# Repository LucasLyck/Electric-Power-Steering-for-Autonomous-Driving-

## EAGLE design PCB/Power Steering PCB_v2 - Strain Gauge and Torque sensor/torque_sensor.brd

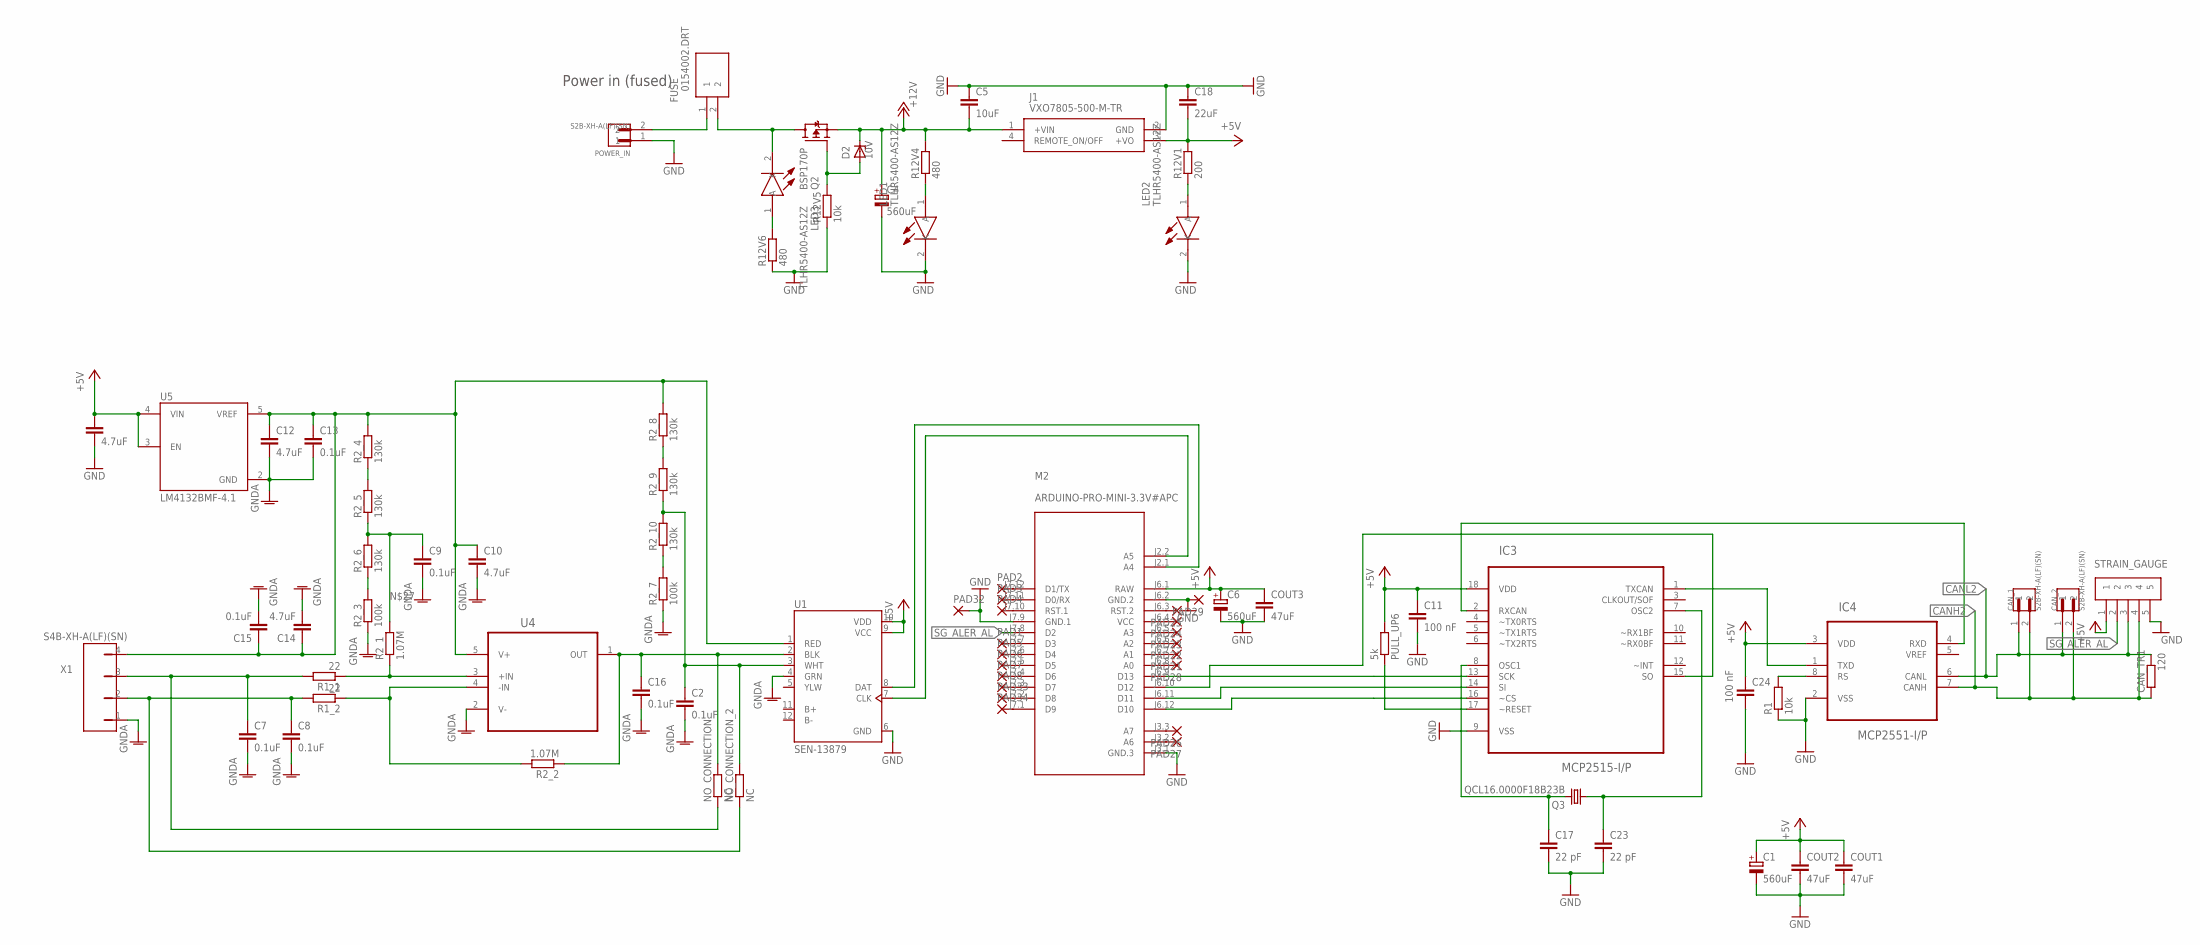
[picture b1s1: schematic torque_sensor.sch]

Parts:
C1, C4, C6: 560uF; PANASONIC_F
C2, C7, C8, C9, C13, C15, C16: 0.1uF; C0805
C3, C10, C12, C14: 4.7uF; C0805
C5: 10uF; C0805
C11, C24: 100 nF; C0805
C17, C23: 22 pF; C0805
C18: 22uF; C0805
CAN_1, CAN_2: S2B-XH-A(LF)(SN); JST_S2B-XH-A(LF)(SN)
CAN_TR1: 120; R0805
COUT1, COUT2, COUT3: 47uF; C0805
D2: 10V; SMB
FUSE: 0154002.DRT; FUSM9750X381N
IC3: MCP2515-I/P; DIP254P762X432-18
IC4: MCP2551-I/P; DIP254P762X432-8
J1: VXO7805-500-M-TR; VXO7805500MTR
LED1, LED2, LED3: TLHR5400-AS12Z; TLHR5400AS12Z
M2: ARDUINO-PRO-MINI-3.3V#APC; ARDUINO-PRO-MINI#APC
NO_CONNECTION: NC; R0805
NO_CONNECTION_2: NC; R0805
PAD1, PAD2, PAD3, PAD4, PAD5, PAD6, PAD7, PAD8, PAD21, PAD22, PAD23, PAD24, PAD25, PAD26, PAD27, PAD28, PAD29, PAD32, PAD33, PAD34: SMD2; SMD1,27-2,54
POWER_IN: S2B-XH-A(LF)(SN); JST_S2B-XH-A(LF)(SN)
PULL_UP6: 5k; R0805
Q2: BSP170P; SOT223
Q3: QCL16.0000F18B23B; HC49/S
R1, R12V5: 10k; R0805
R1_1, R1_2: 22; R0805
R2_1, R2_2: 1.07M; R0805
R2_3, R2_7: 100k; R0805
R2_4, R2_5, R2_6, R2_8, R2_9, R2_10: 130k; R0805
R12V1: 200; R0805
R12V4, R12V6: 480; R0805
STRAIN_GAUGE: S5B-XH-A(LF)(SN); JST_S5B-XH-A(LF)(SN)
U1: SEN-13879; SPARKFUN_SEN-13879
U4: LMP7731MF; SOT95P284X119-5N
U5: LM4132BMF-4.1; SOT95P280X145-5N
X1: S4B-XH-A(LF)(SN)

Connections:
+5V: C1.+, C3.1, C6.+, C11.1, C18.2, C24.1, COUT1.1, COUT2.1, COUT3.1, IC3.18 (VDD), IC4.3 (VDD), J1.3 (+VO), M2.J6.1 (RAW), PULL_UP6.2, R12V1.2, STRAIN_GAUGE.1, U1.9 (VCC), U1.10 (VDD), U5.3 (EN), U5.4 (VIN)
+12V: C4.+, C5.2, D2.C, J1.1 (+VIN), Q2.3 (S), R12V4.2
CANH2: CAN_1.2, CAN_2.2, CAN_TR1.1, IC4.7 (CANH), STRAIN_GAUGE.4
CANL2: CAN_1.1, CAN_2.1, CAN_TR1.2, IC4.6 (CANL), STRAIN_GAUGE.3
GND: C1.-, C3.2, C4.-, C5.1, C6.-, C11.2, C17.2, C18.1, C23.2, C24.2, COUT1.2, COUT2.2, COUT3.2, IC3.9 (VSS), IC4.2 (VSS), J1.2 (GND), LED1.2 (K), LED2.2 (K), M2.J3.1 (GND.3), M2.J6.2 (GND.2), M2.J7.9 (GND.1), PAD29.1, PAD32.1, POWER_IN.1, R1.1, R12V5.1, R12V6.1, STRAIN_GAUGE.5, U1.6 (GND)
GNDA: C2.2, C7.2, C8.2, C9.2, C10.2, C12.2, C13.2, C14.2, C15.2, C16.2, R2_3.1, R2_7.1, U1.4 (GRN), U4.2 (V-), U5.2 (GND), X1.1
unnamed: R2_8.1, R2_9.2
unnamed: LED2.1 (A), R12V1.1
unnamed: LED1.1 (A), R12V4.1
unnamed: C16.1, NO_CONNECTION.2, R2_2.1, U1.2 (BLK), U4.1 (OUT)
unnamed: R1_2.1, R2_2.2, U4.4 (-IN)
unnamed: M2.J7.12 (D1/TX), PAD2.1
unnamed: D2.A, Q2.1 (G), R12V5.2
unnamed: R2_7.2, R2_10.1
unnamed: C10.1, C12.1, C13.1, C14.1, C15.1, R2_4.2, R2_8.2, U1.1 (RED), U4.5 (V+), U5.5 (VREF), X1.4
unnamed: M2.J7.7 (D3), PAD1.1
unnamed: M2.J7.6 (D4), PAD5.1
unnamed: M2.J7.5 (D5), PAD6.1
unnamed: M2.J7.4 (D6), PAD7.1
unnamed: R1_1.1, R2_1.1, U4.3 (+IN)
unnamed: LED3.1 (A), R12V6.2
unnamed: M2.J2.2 (A5), U1.7 (CLK)
unnamed: M2.J7.3 (D7), PAD8.1
unnamed: M2.J7.11 (D0/RX), PAD3.1
unnamed: C2.1, NO_CONNECTION_2.2, R2_9.1, R2_10.2, U1.3 (WHT)
unnamed: M2.J2.1 (A4), U1.8 (DAT)
unnamed: FUSE.1, POWER_IN.2
unnamed: M2.J7.10 (RST.1), PAD4.1
unnamed: FUSE.2, LED3.2 (K), Q2.2 (D), Q2.4 (D)
unnamed: M2.J6.7 (A1), PAD21.1
unnamed: M2.J6.6 (A2), PAD22.1
unnamed: C9.1, R2_1.2, R2_5.1, R2_6.2
unnamed: M2.J6.5 (A3), PAD23.1
unnamed: M2.J6.4 (VCC), PAD24.1
unnamed: M2.J6.3 (RST.2), PAD25.1
unnamed: M2.J3.3 (A7), PAD26.1
unnamed: C8.1, NO_CONNECTION_2.1, R1_2.2, X1.2
unnamed: M2.J7.2 (D8), PAD33.1
unnamed: R2_4.1, R2_5.2
unnamed: IC3.15 (SO), M2.J6.10 (D12)
unnamed: IC3.13 (SCK), M2.J6.9 (D13)
unnamed: IC3.14 (SI), M2.J6.11 (D11)
unnamed: IC3.16 (~CS), M2.J6.12 (D10)
unnamed: M2.J3.2 (A6), PAD27.1
unnamed: M2.J6.8 (A0), PAD28.1
unnamed: R2_3.2, R2_6.1
unnamed: M2.J7.1 (D9), PAD34.1
unnamed: IC3.17 (~RESET), PULL_UP6.1
unnamed: C17.1, IC3.8 (OSC1), Q3.2
unnamed: C23.1, IC3.7 (OSC2), Q3.1
unnamed: IC4.8 (RS), R1.2
unnamed: IC3.2 (RXCAN), IC4.4 (RXD)
unnamed: IC3.1 (TXCAN), IC4.1 (TXD)
SG_ALER_AL: M2.J7.8 (D2), STRAIN_GAUGE.2
VCCINT4: C7.1, NO_CONNECTION.1, R1_1.2, X1.3

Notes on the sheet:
Power in (fused)

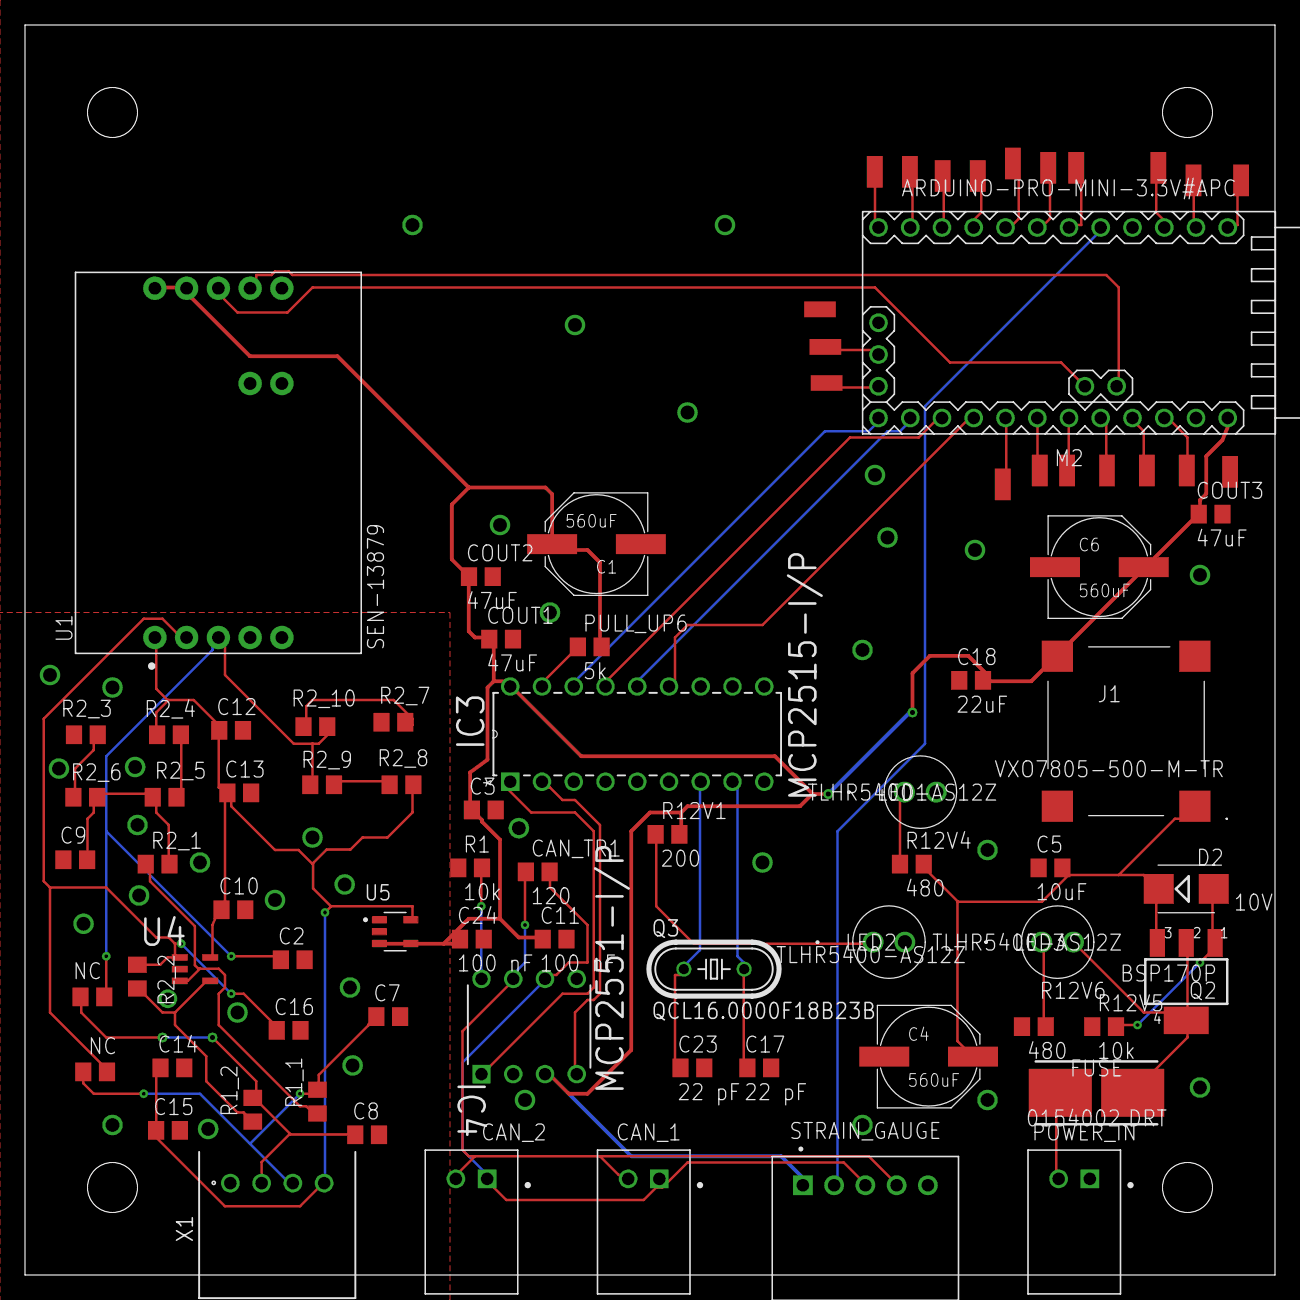
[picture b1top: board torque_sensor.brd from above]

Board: 2 copper layers, 100.0 x 100.0 mm, 83 parts (0 on the bottom side), 55 nets.

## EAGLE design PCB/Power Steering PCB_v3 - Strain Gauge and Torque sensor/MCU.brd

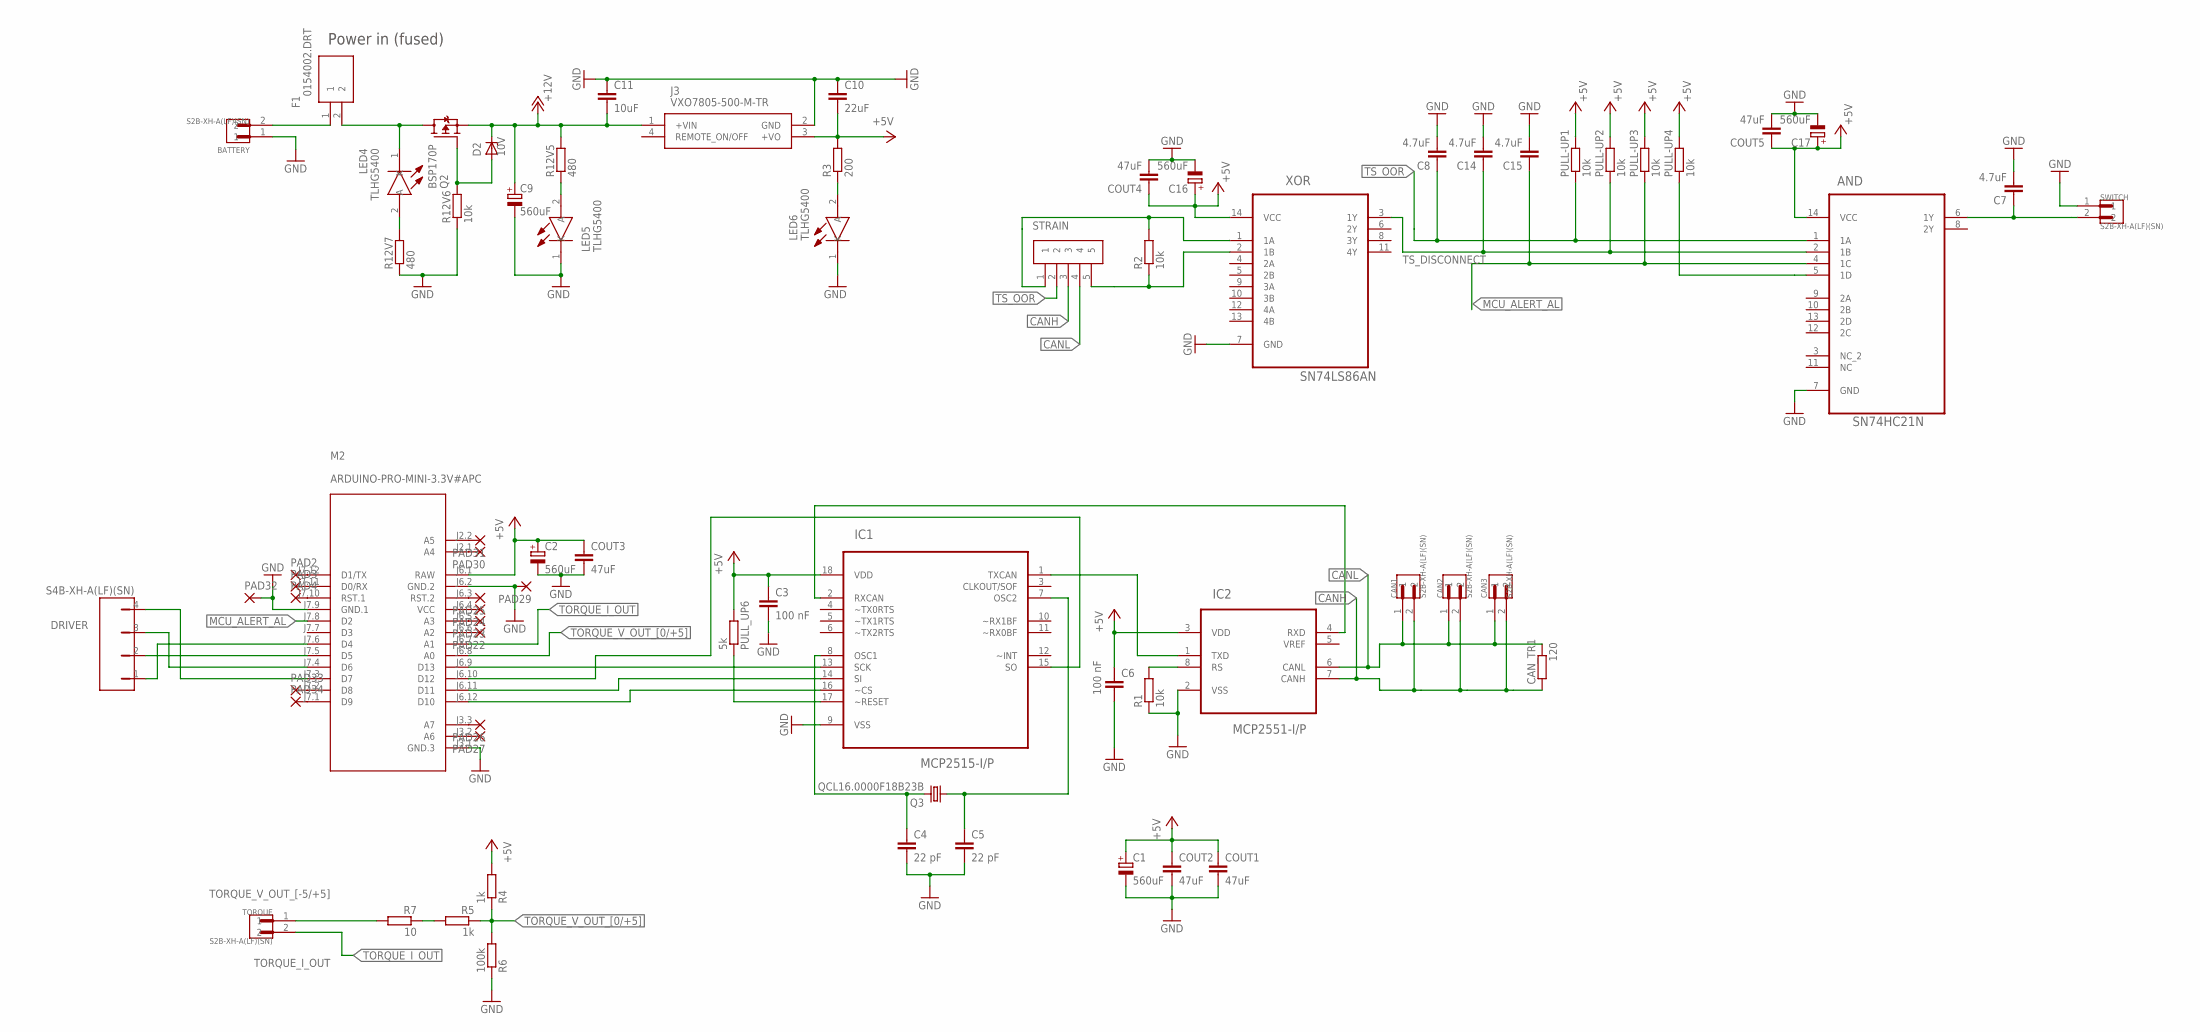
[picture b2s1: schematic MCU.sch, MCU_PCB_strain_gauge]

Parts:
AND: SN74HC21N; DIP254P762X508-14
BATTERY: S2B-XH-A(LF)(SN); JST_S2B-XH-A(LF)(SN)
C1, C2, C9, C16, C17: 560uF; PANASONIC_F
C3, C6: 100 nF; C0805
C4, C5: 22 pF; C0805
C7, C8, C14, C15: 4.7uF; C0805
C10: 22uF; C0805
C11: 10uF; C0805
CAN1, CAN2, CAN3: S2B-XH-A(LF)(SN); JST_S2B-XH-A(LF)(SN)
CAN_TR1: 120; R0805
COUT1, COUT2, COUT3, COUT4, COUT5: 47uF; C0805
D2: 10V; SMB
DRIVER: S4B-XH-A(LF)(SN)
F1: 0154002.DRT; FUSM9750X381N
IC1: MCP2515-I/P; DIP254P762X432-18
IC2: MCP2551-I/P; DIP254P762X432-8
J3: VXO7805-500-M-TR; VXO7805500MTR
LED4, LED5, LED6: TLHG5400
M2: ARDUINO-PRO-MINI-3.3V#APC; ARDUINO-PRO-MINI#APC
PAD2, PAD3, PAD4, PAD22, PAD23, PAD24, PAD25, PAD26, PAD27, PAD29, PAD30, PAD31, PAD32, PAD33, PAD34: SMD2; SMD1,27-2,54
PULL-UP1, PULL-UP2, PULL-UP3, PULL-UP4: 10k; R0805
PULL_UP6: 5k; R0805
Q2: BSP170P; SOT223
Q3: QCL16.0000F18B23B; HC49/S
R1, R2, R12V6: 10k; R0805
R3: 200; R0805
R4, R5: 1k; R0805
R6: 100k; R0805
R7: 10; R0805
R12V5, R12V7: 480; R0805
STRAIN: S5B-XH-A(LF)(SN); JST_S5B-XH-A(LF)(SN)
SWITCH: S2B-XH-A(LF)(SN); JST_S2B-XH-A(LF)(SN)
TORQUE: S2B-XH-A(LF)(SN); JST_S2B-XH-A(LF)(SN)
XOR: SN74LS86AN; DIP254P762X508-14

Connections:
+5V: AND.14 (VCC), C1.+, C2.+, C3.1, C6.1, C10.2, C16.+, C17.+, COUT1.1, COUT2.1, COUT3.1, COUT4.1, COUT5.1, IC1.18 (VDD), IC2.3 (VDD), J3.3 (+VO), M2.J6.1 (RAW), PULL-UP1.2, PULL-UP2.2, PULL-UP3.2, PULL-UP4.2, PULL_UP6.2, R3.2, R4.2, XOR.14 (VCC)
+12V: C9.+, C11.2, D2.C, J3.1 (+VIN), Q2.3 (S), R12V5.2
CANH: CAN1.2, CAN2.2, CAN3.2, CAN_TR1.1, IC2.7 (CANH), STRAIN.3
CANL: CAN1.1, CAN2.1, CAN3.1, CAN_TR1.2, IC2.6 (CANL), STRAIN.4
DRIVER_ALERT_AL: AND.5 (1D), PULL-UP4.1
GND: AND.7 (GND), BATTERY.1, C1.-, C2.-, C3.2, C4.2, C5.2, C6.2, C7.2, C8.2, C9.-, C10.1, C11.1, C14.2, C15.2, C16.-, C17.-, COUT1.2, COUT2.2, COUT3.2, COUT4.2, COUT5.2, IC1.9 (VSS), IC2.2 (VSS), J3.2 (GND), LED5.1 (K), LED6.1 (K), M2.J3.1 (GND.3), M2.J6.2 (GND.2), M2.J7.9 (GND.1), PAD29.1, PAD32.1, R1.1, R6.1, R12V6.1, R12V7.1, SWITCH.1, XOR.7 (GND)
MCU_ALERT_AL: AND.4 (1C), C15.1, M2.J7.8 (D2), PULL-UP3.1
unnamed: LED4.2 (A), R12V7.2
unnamed: DRIVER.4, M2.J7.3 (D7)
unnamed: M2.J7.12 (D1/TX), PAD2.1
unnamed: M2.J7.11 (D0/RX), PAD3.1
unnamed: D2.A, Q2.1 (G), R12V6.2
unnamed: BATTERY.2, F1.1
unnamed: F1.2, LED4.1 (K), Q2.2 (D), Q2.4 (D)
unnamed: M2.J7.10 (RST.1), PAD4.1
unnamed: DRIVER.1, M2.J7.6 (D4)
unnamed: M2.J6.6 (A2), PAD22.1
unnamed: M2.J6.5 (A3), PAD23.1
unnamed: M2.J6.4 (VCC), PAD24.1
unnamed: IC1.15 (SO), M2.J6.10 (D12)
unnamed: M2.J6.3 (RST.2), PAD25.1
unnamed: DRIVER.2, M2.J7.5 (D5)
unnamed: R5.2, R7.1
unnamed: M2.J3.3 (A7), PAD26.1
unnamed: LED5.2 (A), R12V5.1
unnamed: LED6.2 (A), R3.1
unnamed: IC1.13 (SCK), M2.J6.9 (D13)
unnamed: IC1.14 (SI), M2.J6.11 (D11)
unnamed: IC1.16 (~CS), M2.J6.12 (D10)
unnamed: DRIVER.3, M2.J7.4 (D6)
unnamed: M2.J3.2 (A6), PAD27.1
unnamed: M2.J2.1 (A4), PAD30.1
unnamed: M2.J2.2 (A5), PAD31.1
unnamed: M2.J7.2 (D8), PAD33.1
unnamed: M2.J7.1 (D9), PAD34.1
unnamed: IC1.17 (~RESET), PULL_UP6.1
unnamed: C4.1, IC1.8 (OSC1), Q3.2
unnamed: C5.1, IC1.7 (OSC2), Q3.1
unnamed: IC2.8 (RS), R1.2
unnamed: IC1.2 (RXCAN), IC2.4 (RXD)
unnamed: R2.2, STRAIN.1, XOR.1 (1A)
unnamed: AND.6 (1Y), C7.1, SWITCH.2
unnamed: R2.1, STRAIN.5, XOR.2 (1B)
unnamed: IC1.1 (TXCAN), IC2.1 (TXD)
TORQUE_I_OUT: M2.J6.7 (A1), TORQUE.2
TORQUE_V_OUT_[0/+5]: M2.J6.8 (A0), R4.1, R5.1, R6.2
TORQUE_V_OUT_[-5/+5]: R7.2, TORQUE.1
TS_DISCONNECT: AND.2 (1B), C14.1, PULL-UP2.1, XOR.3 (1Y)
TS_OOR: AND.1 (1A), C8.1, PULL-UP1.1, STRAIN.2

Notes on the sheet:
Power in (fused)

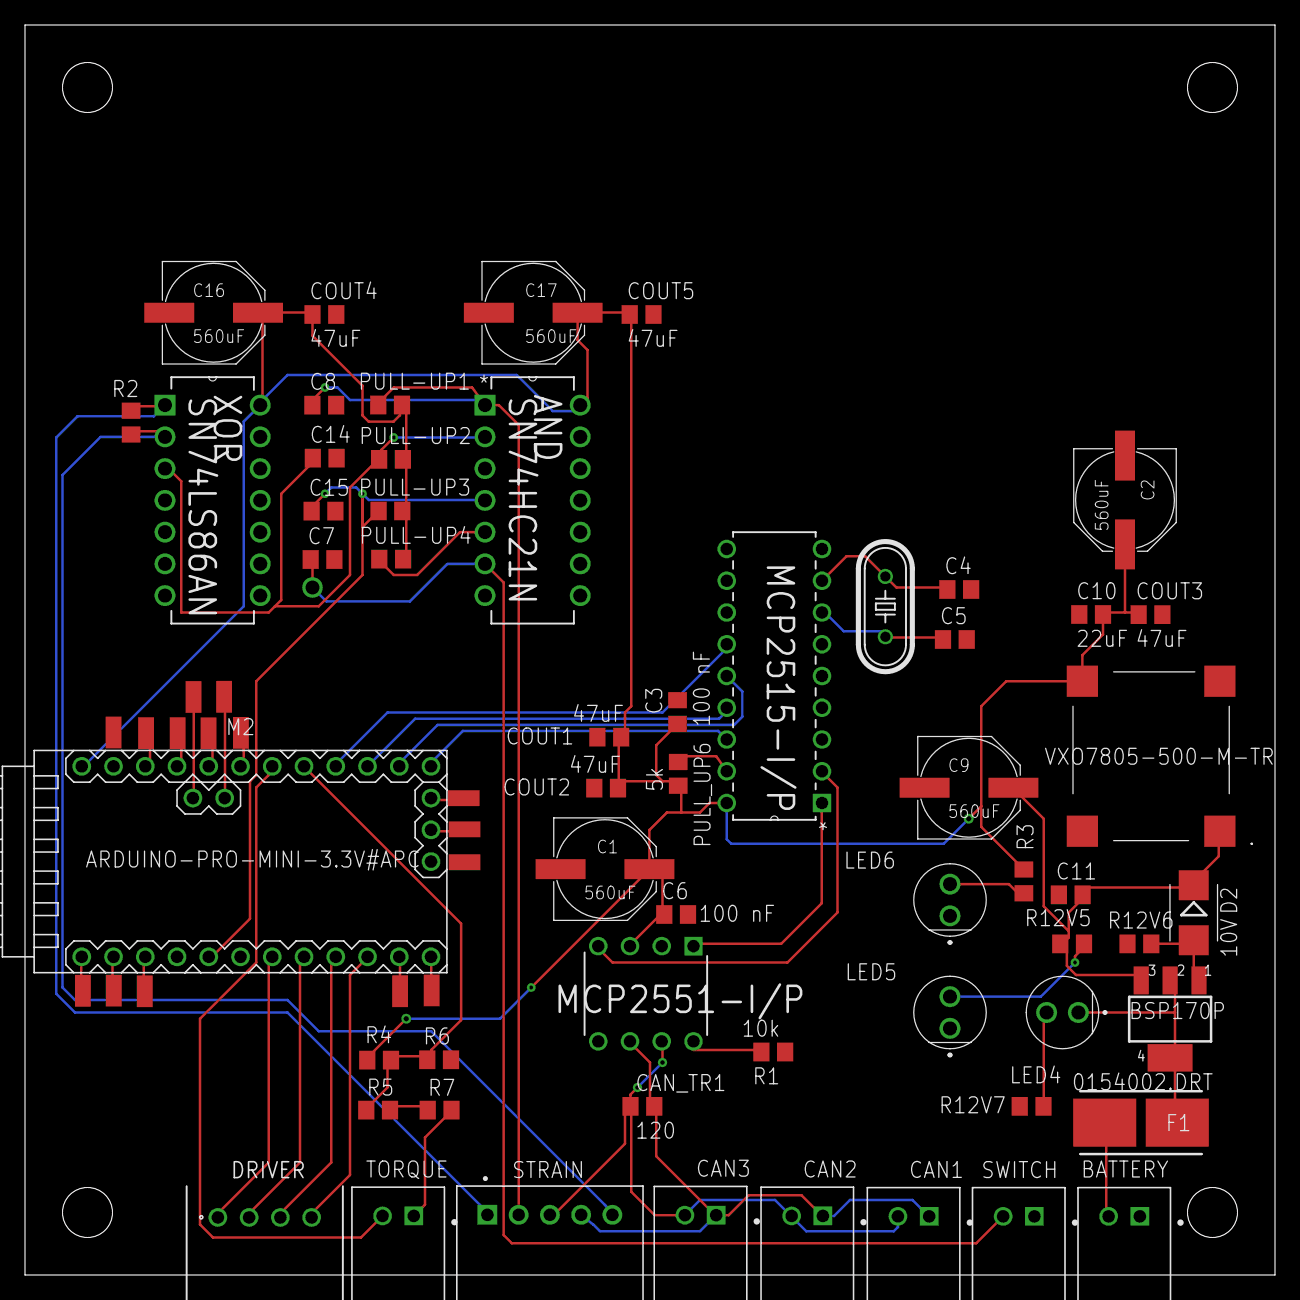
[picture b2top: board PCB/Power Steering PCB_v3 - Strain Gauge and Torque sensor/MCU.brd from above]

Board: 2 copper layers, 100.0 x 100.0 mm, 72 parts (0 on the bottom side), 49 nets.

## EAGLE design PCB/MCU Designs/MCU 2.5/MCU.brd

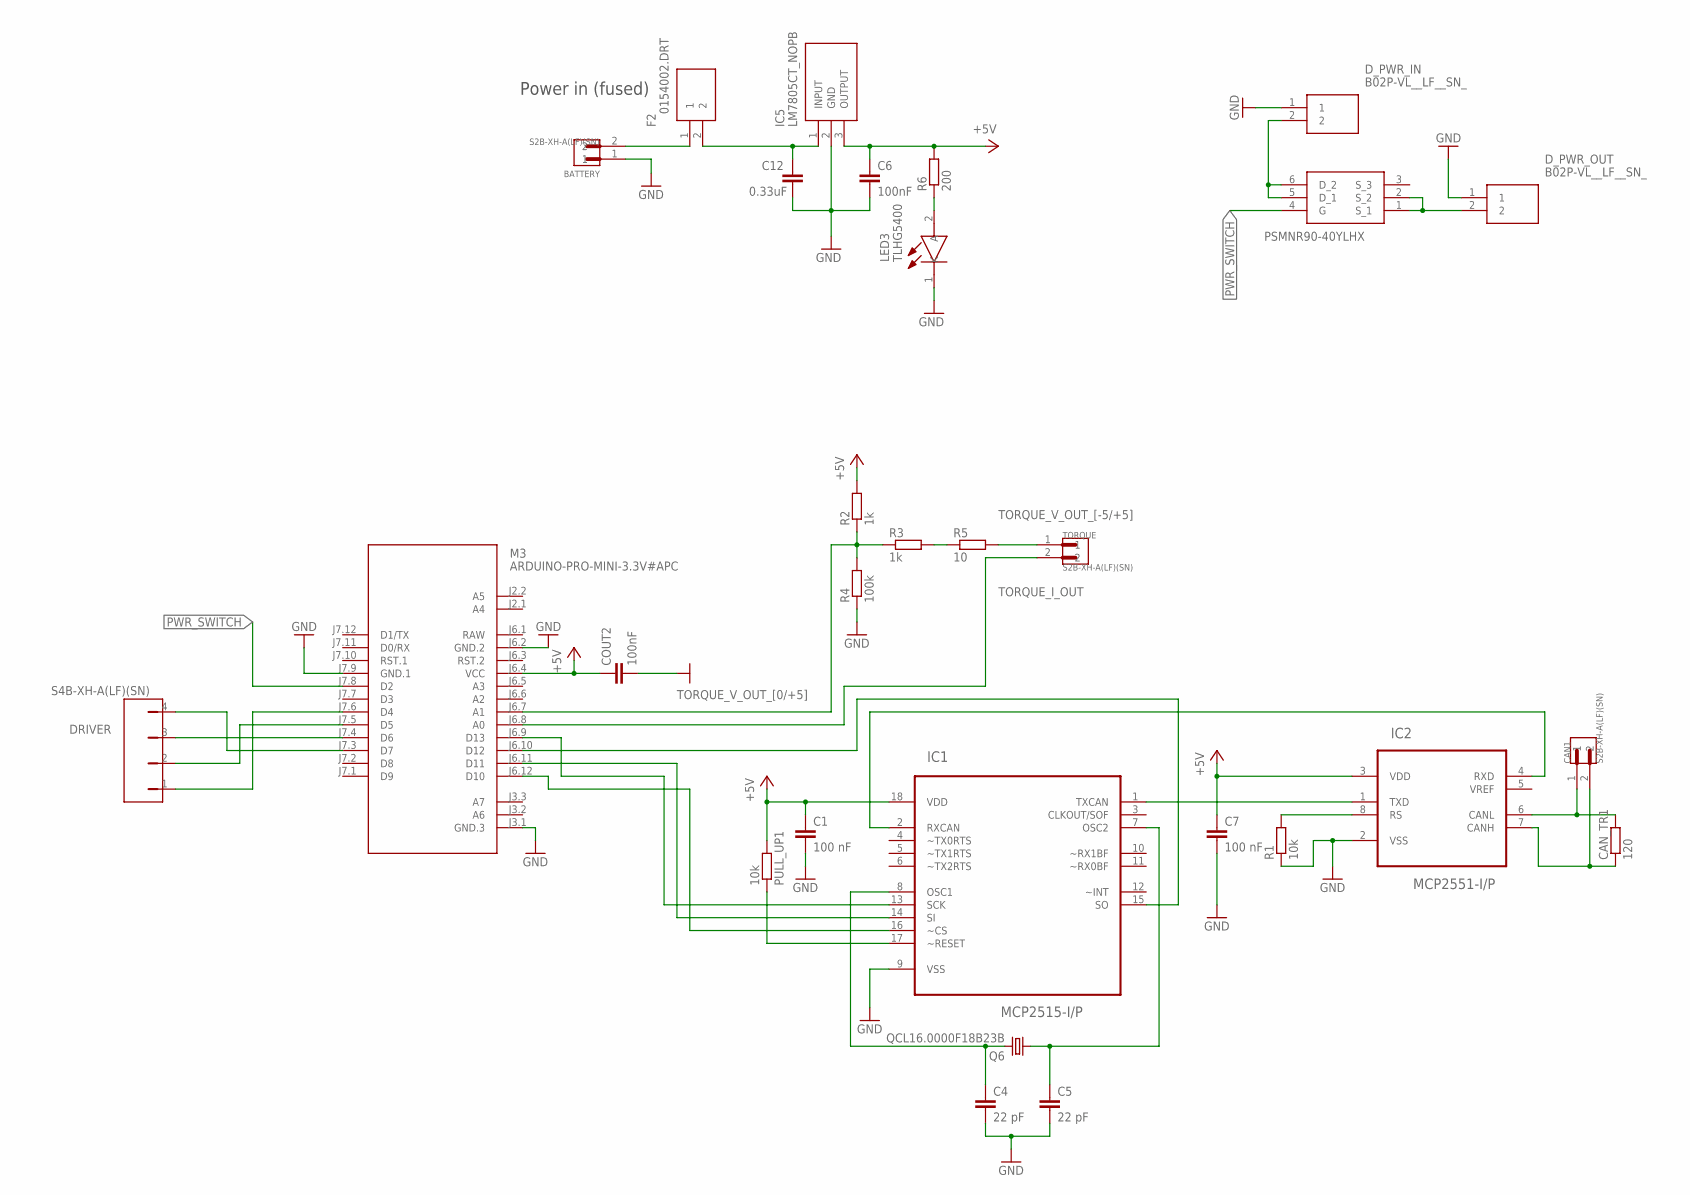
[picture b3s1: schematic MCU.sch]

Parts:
BATTERY: S2B-XH-A(LF)(SN); JST_S2B-XH-A(LF)(SN)
C1, C7: 100 nF; C0805
C4, C5: 22 pF; C0805
C6: 100nF; C0805
C12: 0.33uF; C0805
CAN1: S2B-XH-A(LF)(SN); JST_S2B-XH-A(LF)(SN)
CAN_TR1: 120; R0805
COUT2: 100nF; C0805
DRIVER: S4B-XH-A(LF)(SN)
D_PWR_IN: B02P-VL__LF__SN_; SHDR2W180P0X620_1X2_1340X1320X
D_PWR_OUT: B02P-VL__LF__SN_; SHDR2W180P0X620_1X2_1340X1320X
F2: 0154002.DRT; FUSM9750X381N
IC1: MCP2515-I/P; DIP254P762X432-18
IC2: MCP2551-I/P; DIP254P762X432-8
IC5: LM7805CT_NOPB; TO254P470X1028X1955-3P
LED3: TLHG5400
M3: ARDUINO-PRO-MINI-3.3V#APC; ARDUINO-PRO-MINI#APC
PULL_UP1: 10k; R0805
Q1: PSMNR90-40YLHX; PSMNR9040YLHX
Q6: QCL16.0000F18B23B; HC49/S
R1: 10k; R0805
R2, R3: 1k; R0805
R4: 100k; R0805
R5: 10; R0805
R6: 200; R0805
TORQUE: S2B-XH-A(LF)(SN); JST_S2B-XH-A(LF)(SN)

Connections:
+5V: C1.1, C6.1, C7.1, COUT2.1, IC1.18 (VDD), IC2.3 (VDD), IC5.3 (OUTPUT), M3.J6.4 (VCC), PULL_UP1.2, R2.2, R6.2
CANH1: CAN1.1, CAN_TR1.2, IC2.6 (CANL)
CANL1: CAN1.2, CAN_TR1.1, IC2.7 (CANH)
DRAIN: D_PWR_IN.2, Q1.5 (D_1), Q1.6 (D_2)
GND: BATTERY.1, C1.2, C4.2, C5.2, C6.2, C7.2, C12.2, COUT2.2, D_PWR_IN.1, D_PWR_OUT.1, IC1.9 (VSS), IC2.2 (VSS), IC5.2 (GND), LED3.1 (K), M3.J3.1 (GND.3), M3.J6.2 (GND.2), M3.J7.9 (GND.1), R1.1, R4.1
unnamed: DRIVER.4, M3.J7.3 (D7)
unnamed: DRIVER.2, M3.J7.5 (D5)
unnamed: C5.1, IC1.7 (OSC2), Q6.1
unnamed: DRIVER.3, M3.J7.4 (D6)
unnamed: IC1.17 (~RESET), PULL_UP1.1
unnamed: DRIVER.1, M3.J7.6 (D4)
unnamed: R3.2, R5.1
unnamed: BATTERY.2, F2.1
unnamed: LED3.2 (A), R6.1
unnamed: C12.1, F2.2, IC5.1 (INPUT)
unnamed: IC1.1 (TXCAN), IC2.1 (TXD)
unnamed: IC1.2 (RXCAN), IC2.4 (RXD)
unnamed: C4.1, IC1.8 (OSC1), Q6.2
unnamed: IC2.8 (RS), R1.2
unnamed: IC1.15 (SO), M3.J6.10 (D12)
unnamed: IC1.14 (SI), M3.J6.11 (D11)
unnamed: IC1.16 (~CS), M3.J6.12 (D10)
unnamed: IC1.13 (SCK), M3.J6.9 (D13)
PWR_SWITCH: M3.J7.8 (D2), Q1.4 (G)
RAW: M3.J6.1 (RAW)
SOURCE: D_PWR_OUT.2, Q1.1 (S_1), Q1.2 (S_2)
TORQUE_I_OUT: M3.J6.8 (A0), TORQUE.2
TORQUE_V_OUT_[0/+5]: M3.J6.7 (A1), R2.1, R3.1, R4.2
TORQUE_V_OUT_[-5/+5]: R5.2, TORQUE.1

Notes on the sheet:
Power in (fused)

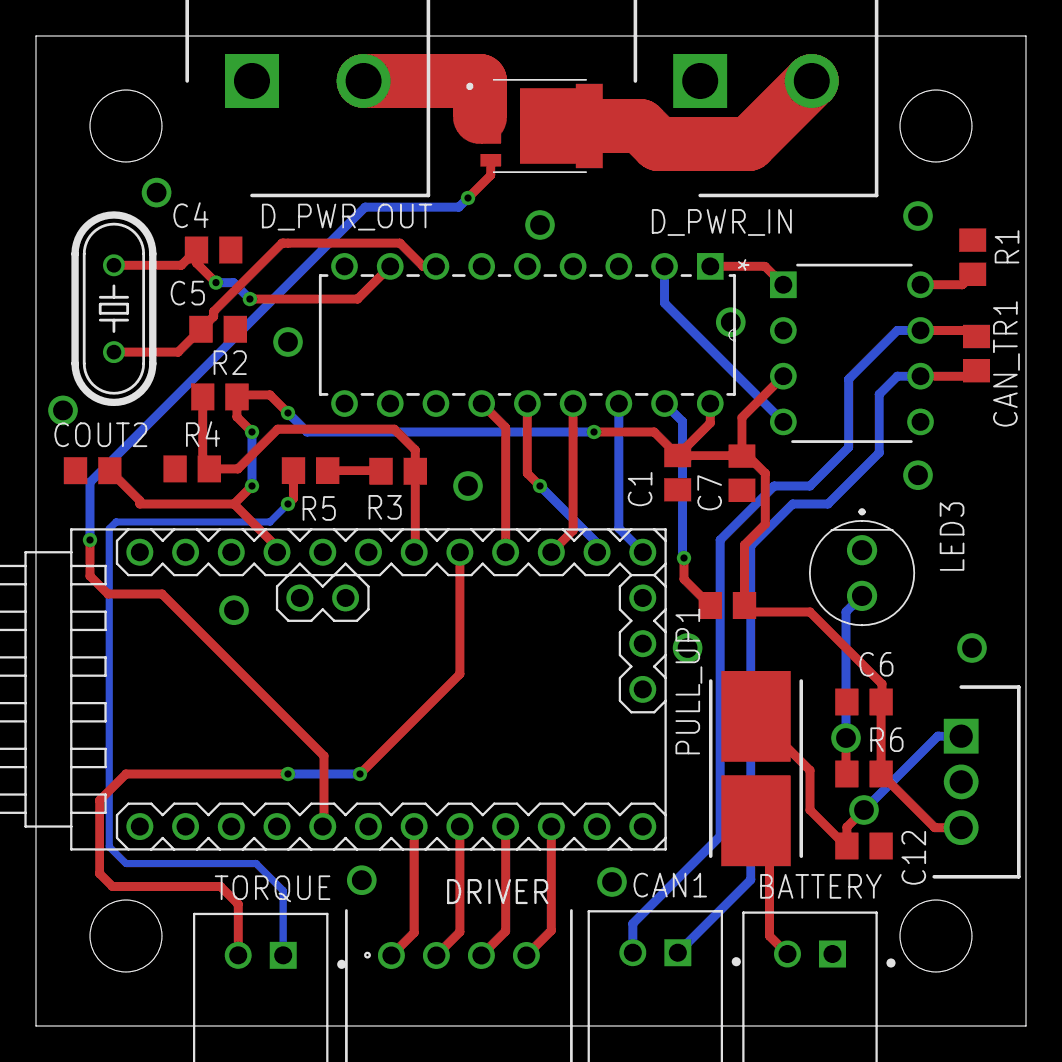
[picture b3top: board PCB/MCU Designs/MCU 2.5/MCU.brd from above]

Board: 2 copper layers, 55.0 x 55.0 mm, 29 parts (0 on the bottom side), 28 nets.

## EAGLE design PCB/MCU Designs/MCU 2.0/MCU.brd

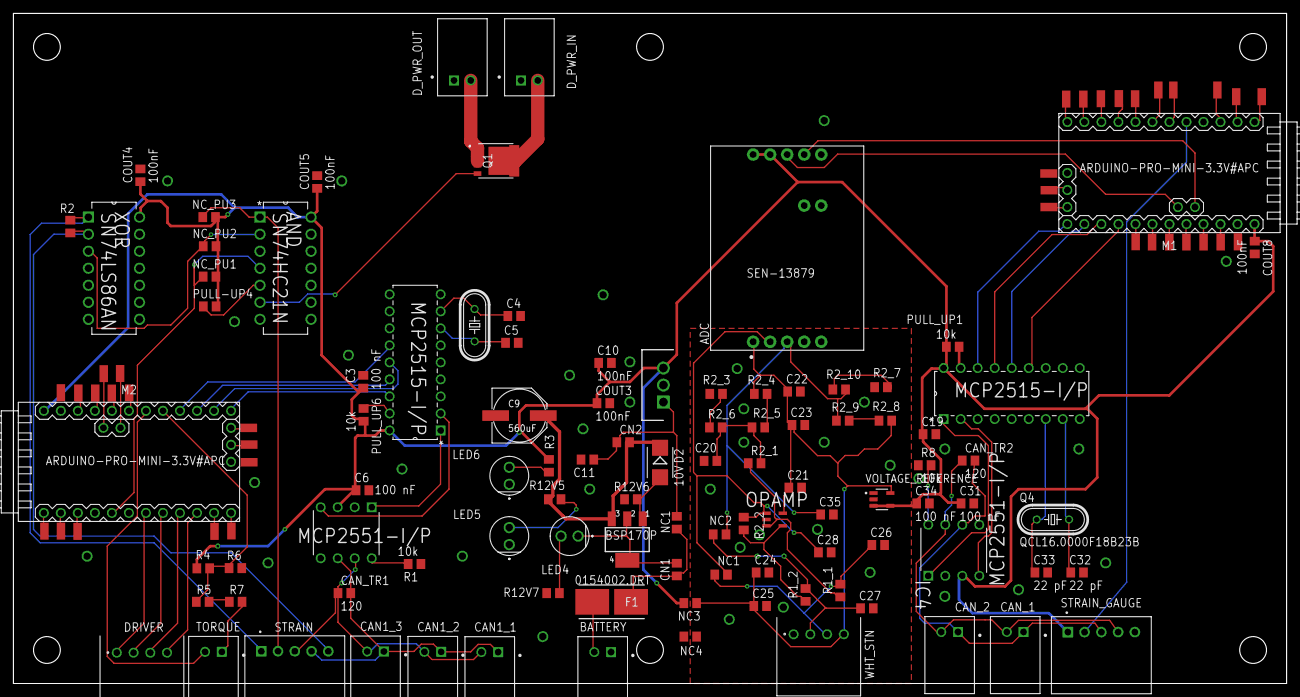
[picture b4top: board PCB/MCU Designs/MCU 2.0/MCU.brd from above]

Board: 2 copper layers, 190.0 x 100.0 mm, 133 parts (0 on the bottom side), 99 nets.

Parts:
ADC: SEN-13879; SPARKFUN_SEN-13879
AND: SN74HC21N; DIP254P762X508-14
BATTERY: S2B-XH-A(LF)(SN); JST_S2B-XH-A(LF)(SN)
C3, C6, C31, C34: 100 nF; C0805
C4, C5, C32, C33: 22 pF; C0805
C9: 560uF; PANASONIC_F
C10, C20, C23, C25, C26, C27, C28, C35: 100nF; C0805
C11: 0.33uF; C0805
C19, C21, C22, C24: 4.7uF; C0805
CAN1_1, CAN1_2, CAN1_3: S2B-XH-A(LF)(SN); JST_S2B-XH-A(LF)(SN)
CAN_1, CAN_2: S2B-XH-A(LF)(SN); JST_S2B-XH-A(LF)(SN)
CAN_TR1, CAN_TR2: 120; R0805
CN1, CN2: 10k; R0805
COUT3, COUT4, COUT5, COUT8: 100nF; C0805
D2: 10V; SMB
DRIVER: S4B-XH-A(LF)(SN)
D_PWR_IN: S2B-XH-A(LF)(SN); JST_S2B-XH-A(LF)(SN)
D_PWR_OUT: S2B-XH-A(LF)(SN); JST_S2B-XH-A(LF)(SN)
F1: 0154002.DRT; FUSM9750X381N
IC1, IC3: MCP2515-I/P; DIP254P762X432-18
IC2, IC4: MCP2551-I/P; DIP254P762X432-8
IC5: LM7805CT_NOPB; TO254P470X1028X1955-3P
LED4, LED5, LED6: TLHG5400
M1, M2: ARDUINO-PRO-MINI-3.3V#APC; ARDUINO-PRO-MINI#APC
NC1: 10k; R0805
NC3, NC4: R0805
NC_PU1, NC_PU2, NC_PU3: 10k; R0805
NO_CONNECTION: NC1; R0805
NO_CONNECTION_2: NC2; R0805
OPAMP: LMP7731MF; SOT95P284X119-5N
PAD1, PAD2, PAD3, PAD4, PAD5, PAD6, PAD7, PAD8, PAD9, PAD10, PAD11, PAD12, PAD13, PAD14, PAD15, PAD16, PAD17, PAD18, PAD19, PAD20, PAD21, PAD22, PAD23, PAD24, PAD25, PAD26, PAD27, PAD28, PAD29, PAD30, PAD31, PAD32, PAD33, PAD34, PAD35: SMD1,27-2,54
PULL-UP4: 10k; R0805
PULL_UP1, PULL_UP6: 10k; R0805
Q1: PSMNR90-40YLHX; PSMNR9040YLHX
Q2: BSP170P; SOT223
Q3, Q4: QCL16.0000F18B23B; HC49/S
R1, R2, R8, R12V6: 10k; R0805
R1_1, R1_2: 22; R0805
R2_1, R2_2: 1.07M; R0805
R2_3, R2_7, R6: 100k; R0805
R2_4, R2_5, R2_6, R2_8, R2_9, R2_10: 130k; R0805
R3: 200; R0805
R4, R5: 1k; R0805
R7: 10; R0805
R12V5, R12V7: 480; R0805
STRAIN: S5B-XH-A(LF)(SN); JST_S5B-XH-A(LF)(SN)
STRAIN_GAUGE: S5B-XH-A(LF)(SN); JST_S5B-XH-A(LF)(SN)
TORQUE: S2B-XH-A(LF)(SN); JST_S2B-XH-A(LF)(SN)
VOLTAGE_REFERENCE: LM4132BMF-4.1; SOT95P280X145-5N
WHT_STN: S4B-XH-A(LF)(SN)
XOR: SN74LS86AN; DIP254P762X508-14

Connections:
+5V: ADC.9, ADC.10, AND.14, C3.1, C6.1, C10.1, C19.1, C31.1, C34.1, COUT3.1, COUT4.1, COUT5.1, COUT8.1, IC1.18, IC2.3, IC3.18, IC4.3, IC5.3, M1.J6.1, M2.J6.1, NC3.2, NC_PU1.2, NC_PU2.2, NC_PU3.2, PULL-UP4.2, PULL_UP1.2, PULL_UP6.2, R3.2, R4.2, STRAIN_GAUGE.1, VOLTAGE_REFERENCE.3, VOLTAGE_REFERENCE.4, XOR.14
+12V: C9.+, CN2.2, D2.C, Q2.3, R12V5.2
CANH1: CAN1_1.2, CAN1_2.2, CAN1_3.2, CAN_TR1.1, IC2.7, STRAIN.3
CANH2: CAN_1.2, CAN_2.2, CAN_TR2.1, IC4.7, STRAIN_GAUGE.4
CANL1: CAN1_1.1, CAN1_2.1, CAN1_3.1, CAN_TR1.2, IC2.6, STRAIN.4
CANL2: CAN_1.1, CAN_2.1, CAN_TR2.2, IC4.6, STRAIN_GAUGE.3
DRAIN: D_PWR_IN.2, Q1.5, Q1.6
DRIVER_ALERT_AL: AND.5, PULL-UP4.1
GND: ADC.6, AND.7, BATTERY.1, C3.2, C4.2, C5.2, C6.2, C9.-, C10.2, C11.2, C19.2, C31.2, C32.2, C33.2, C34.2, COUT3.2, COUT4.2, COUT5.2, COUT8.2, D_PWR_IN.1, D_PWR_OUT.1, IC1.9, IC2.2, IC3.9, IC4.2, LED5.1, LED6.1, M1.J3.1, M1.J6.2, M1.J7.9, M2.J3.1, M2.J6.2, M2.J7.9, NC4.1, PAD13.1, PAD14.1, PAD29.1, PAD32.1, R1.1, R6.1, R8.1, R12V6.1, R12V7.1, STRAIN_GAUGE.5, XOR.7
GNDA: ADC.4, C20.2, C21.2, C22.2, C23.2, C24.2, C25.2, C26.2, C27.2, C28.2, C35.2, NC4.2, OPAMP.2, R2_3.1, R2_7.1, VOLTAGE_REFERENCE.2, WHT_STN.1
MCU_ALERT_AL: AND.4, M2.J7.8, NC_PU1.1
unnamed: LED4.2, R12V7.2
unnamed: DRIVER.4, M2.J7.3
unnamed: M2.J7.12, PAD2.1
unnamed: M2.J7.11, PAD3.1
unnamed: D2.A, Q2.1, R12V6.2
unnamed: BATTERY.2, F1.1
unnamed: CN1.1, LED4.1, Q2.2, Q2.4
unnamed: M2.J7.10, PAD4.1
unnamed: DRIVER.1, M2.J7.6
unnamed: M2.J6.6, PAD22.1
unnamed: M2.J6.5, PAD23.1
unnamed: M2.J6.4, PAD24.1
unnamed: IC1.15, M2.J6.10
unnamed: M2.J6.3, PAD25.1
unnamed: DRIVER.2, M2.J7.5
unnamed: R5.2, R7.1
unnamed: M2.J3.3, PAD26.1
unnamed: LED5.2, R12V5.1
unnamed: LED6.2, R3.1
unnamed: IC1.13, M2.J6.9
unnamed: IC1.14, M2.J6.11
unnamed: IC1.16, M2.J6.12
unnamed: DRIVER.3, M2.J7.4
unnamed: CN1.2, F1.2, NC1.2
unnamed: C11.1, CN2.1, IC5.1, NC1.1
unnamed: C20.1, R2_1.2, R2_5.1, R2_6.2
unnamed: ADC.2, C28.1, NO_CONNECTION.2, OPAMP.1, R2_2.1
unnamed: OPAMP.4, R1_2.1, R2_2.2
unnamed: OPAMP.3, R1_1.1, R2_1.1
unnamed: R2_3.2, R2_6.1
unnamed: M1.J7.12, PAD1.1
unnamed: M1.J7.11, PAD5.1
unnamed: M1.J7.10, PAD6.1
unnamed: R2_4.1, R2_5.2
unnamed: M1.J6.7, PAD21.1
unnamed: M1.J6.6, PAD7.1
unnamed: M1.J6.5, PAD8.1
unnamed: M1.J6.4, PAD9.1
unnamed: M2.J3.2, PAD27.1
unnamed: M1.J6.3, PAD10.1
unnamed: M2.J2.1, PAD30.1
unnamed: M1.J3.3, PAD11.1
unnamed: M1.J3.2, PAD12.1
unnamed: M1.J6.8, PAD28.1
unnamed: M1.J7.2, PAD15.1
unnamed: M1.J7.1, PAD16.1
unnamed: IC3.17, PULL_UP1.1
unnamed: M2.J2.2, PAD31.1
unnamed: C32.1, IC3.8, Q4.2
unnamed: C33.1, IC3.7, Q4.1
unnamed: IC4.8, R8.2
unnamed: IC3.2, IC4.4
unnamed: M2.J7.2, PAD33.1
unnamed: M2.J7.1, PAD34.1
unnamed: IC1.17, PULL_UP6.1
unnamed: IC3.1, IC4.1
unnamed: C4.1, IC1.8, Q3.2
unnamed: C5.1, IC1.7, Q3.1
unnamed: IC2.8, R1.2
unnamed: IC3.15, M1.J6.10
unnamed: IC1.2, IC2.4
unnamed: R2.2, STRAIN.1, XOR.1
unnamed: IC3.13, M1.J6.9
unnamed: IC3.14, M1.J6.11
unnamed: R2.1, STRAIN.5, XOR.2
unnamed: IC1.1, IC2.1
unnamed: IC3.16, M1.J6.12
unnamed: ADC.7, M1.J2.2
unnamed: ADC.8, M1.J2.1
unnamed: R2_8.1, R2_9.2
unnamed: R2_7.2, R2_10.1
unnamed: M1.J7.7, PAD17.1
unnamed: M1.J7.6, PAD18.1
unnamed: M1.J7.5, PAD19.1
unnamed: M1.J7.4, PAD20.1
unnamed: M1.J7.3, PAD35.1
unnamed: C27.1, NO_CONNECTION_2.1, R1_2.2, WHT_STN.2
unnamed: ADC.3, C35.1, NO_CONNECTION_2.2, R2_9.1, R2_10.2
unnamed: ADC.1, C21.1, C22.1, C23.1, C24.1, C25.1, NC3.1, OPAMP.5, R2_4.2, R2_8.2, VOLTAGE_REFERENCE.5, WHT_STN.4
PWR_SWITCH: AND.6, Q1.4
SG_ALER_AL: M1.J7.8, STRAIN_GAUGE.2
SOURCE: D_PWR_OUT.2, Q1.1, Q1.2
TORQUE_I_OUT: M2.J6.7, TORQUE.2
TORQUE_V_OUT_[0/+5]: M2.J6.8, R4.1, R5.1, R6.2
TORQUE_V_OUT_[-5/+5]: R7.2, TORQUE.1
TS_DISCONNECT: AND.2, NC_PU2.1, XOR.3
TS_OOR: AND.1, NC_PU3.1, STRAIN.2
VCCINT4: C26.1, NO_CONNECTION.1, R1_1.2, WHT_STN.3

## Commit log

2020-06-20 added something
2020-06-23 Added paper

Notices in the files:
parts and their libraries:
diy-modules: Released under the Creative Commons Attribution 4.0 International License: http://creativecommons.org/licenses/by/4.0
